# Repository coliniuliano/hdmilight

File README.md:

# HDMI Light v3

Ambilight for a 4K TV, with no PC and no plugin in your media player. One small board sits between your HDMI
source and the TV, watches the picture going past, and drives an LED strip behind the screen so the wall glows
the colours at the edges of the image — in real time, whatever the source is.

## How it works

```mermaid
flowchart LR
    S[HDMI source] --> G[HDMI splitter]
    G -->|4K60, untouched| TV[TV]
    G -->|1080p copy| M[capture chip]
    M -->|USB video| E[ESP32]
    E --> L[LED strip]
```

- An **HDMI splitter** (GSV2001) sends the picture straight on to the TV — 4K60 with HDR, nothing re-encoded or
  delayed — and makes a second, smaller copy. It answers the source's HDCP 2.2, so streaming boxes are happy.
- A **capture chip** (MS2130) turns that copy into a USB video stream, the way a cheap capture stick does.
- An **ESP32-S31** decodes it 30 times a second and drives the strip. `core/` is
  [HyperHDR](https://github.com/awawa-dev/HyperHDR)'s colour pipeline recompiled for a microcontroller — the same
  HDR tone mapping, black-bar detection and smoothing, rewritten in portable C (MIT, `core/LICENSE.HyperHDR`).

All three sit on one 78 × 60 mm board. You set it up from a web page it serves, and it appears in Home Assistant
as a light. The LEDs never depend on your network: unplug the router and they keep following the picture.

## Getting one going

You need the board, a 5 V 1.5 A USB-C supply, two HDMI cables, and a WS2812, WS2815, WS2811 or SK6812 RGBW strip
on its own 5 V supply with the grounds joined and data into J4. (94 LEDs at full white draw about 5.6 A, so
brightness is capped at 60 % by default.)

**Order the board** at [JLCPCB](https://jlcpcb.com): zip up `hardware/fab/gerbers/` and upload it — 4 layers,
1.6 mm, stackup JLC04161H-7628, impedance control, top-side assembly — with `fab/bom_jlcpcb.csv` and
`fab/cpl_jlcpcb.csv`, and check the rotations in their placement preview. Four parts come back unfitted and go on
by hand: the splitter U2 (QFN-76, hot air), the ESP32 module U1, and the headers J4 and J5.

**Flash it** with [ESP-IDF](https://docs.espressif.com/projects/esp-idf/) 6.1 or newer:

```bash
cd firmware && ./idf-oneboard.sh set-target esp32s31 && ./idf-oneboard.sh build
```

```bash
./idf-oneboard.sh -p /dev/cu.usbmodem* flash monitor
```

The capture chip's own flash arrives blank and is written once over the same cable with
`tools/ms2130_serial.py write <image>`. Later updates go over Wi-Fi (`tools/ota_paced.py`), into one of two app
slots, and roll back on their own if the new image cannot reach the network.

**Set it up**: the board puts up its own Wi-Fi network, `hdmilight-xxxx`, password `hdmilight`, with a page at
`http://192.168.4.1`. Pick your network and a name and it answers at `http://<name>.local/` from then on — live
view, strip layout, brightness, colour, HDR, logs, self-test and updates, all also under `/api/`. There is no
password on that page, so keep the board on a network you trust.

The LEDs fade out shortly after the TV goes to standby and come back when it wakes (the page has TV on/off
buttons over CEC), and two seconds after the picture stops.

## What is in here

| Folder | |
|---|---|
| `firmware/` | the ESP-IDF project; `main/www/index.html` is the whole web UI |
| `core/` | the colour pipeline — portable C, no ESP-IDF, tested on the host |
| `hardware/` | the board: a KiCad project generated by the scripts in `gen/`, order files in `fab/` |
| `gsv2001/` | the HDMI splitter driver, its tests, and the tools that check it against the real thing |
| `ms2130/` | tools for the capture chip's flash image |
| `tools/` | updating, flashing, crash decoding and host tests |

Everything is testable without hardware; `make -C core test` and `make -C gsv2001 check` matter most.

---

The board — netlist, hand-scripted routing, fabrication files — and its firmware were made with Claude Fable 5.2,
which also brought the first one up with Colin at the bench.

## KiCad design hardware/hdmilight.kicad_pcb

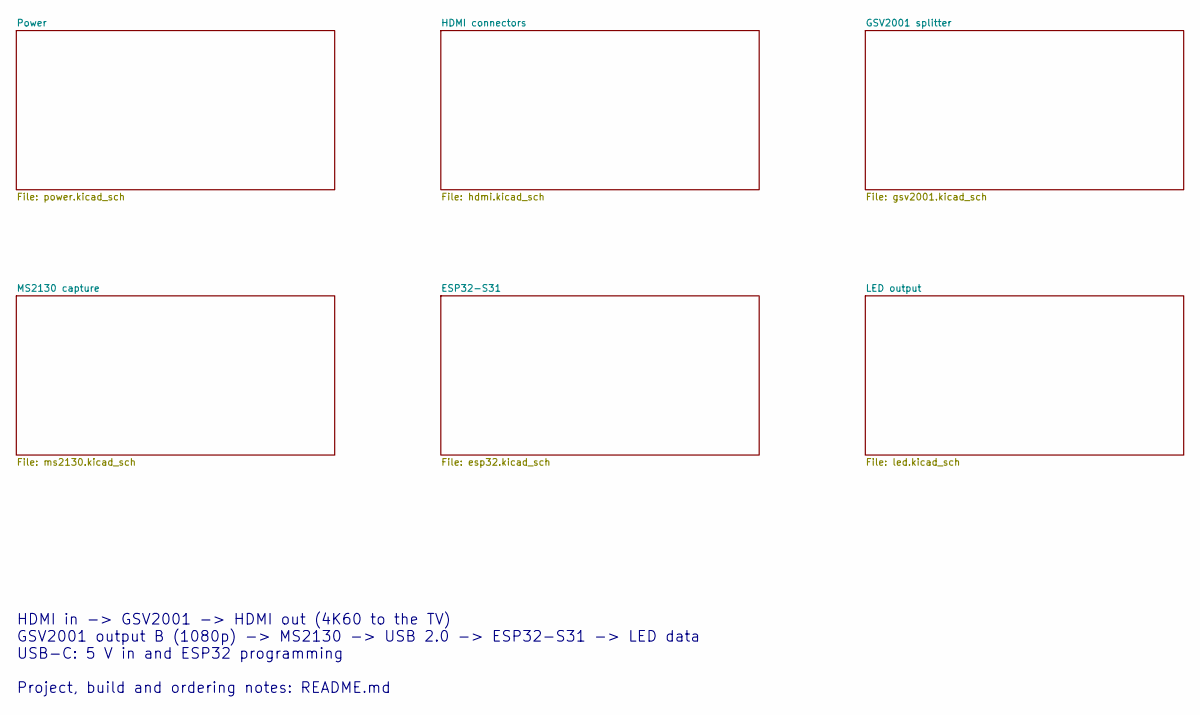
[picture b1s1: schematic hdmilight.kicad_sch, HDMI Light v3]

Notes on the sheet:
HDMI in -> GSV2001 -> HDMI out (4K60 to the TV) GSV2001 output B (1080p) -> MS2130 -> USB 2.0 -> ESP32-S31 -> LED data USB-C: 5 V in and ESP32 programming Project, build and ordering notes: README.md

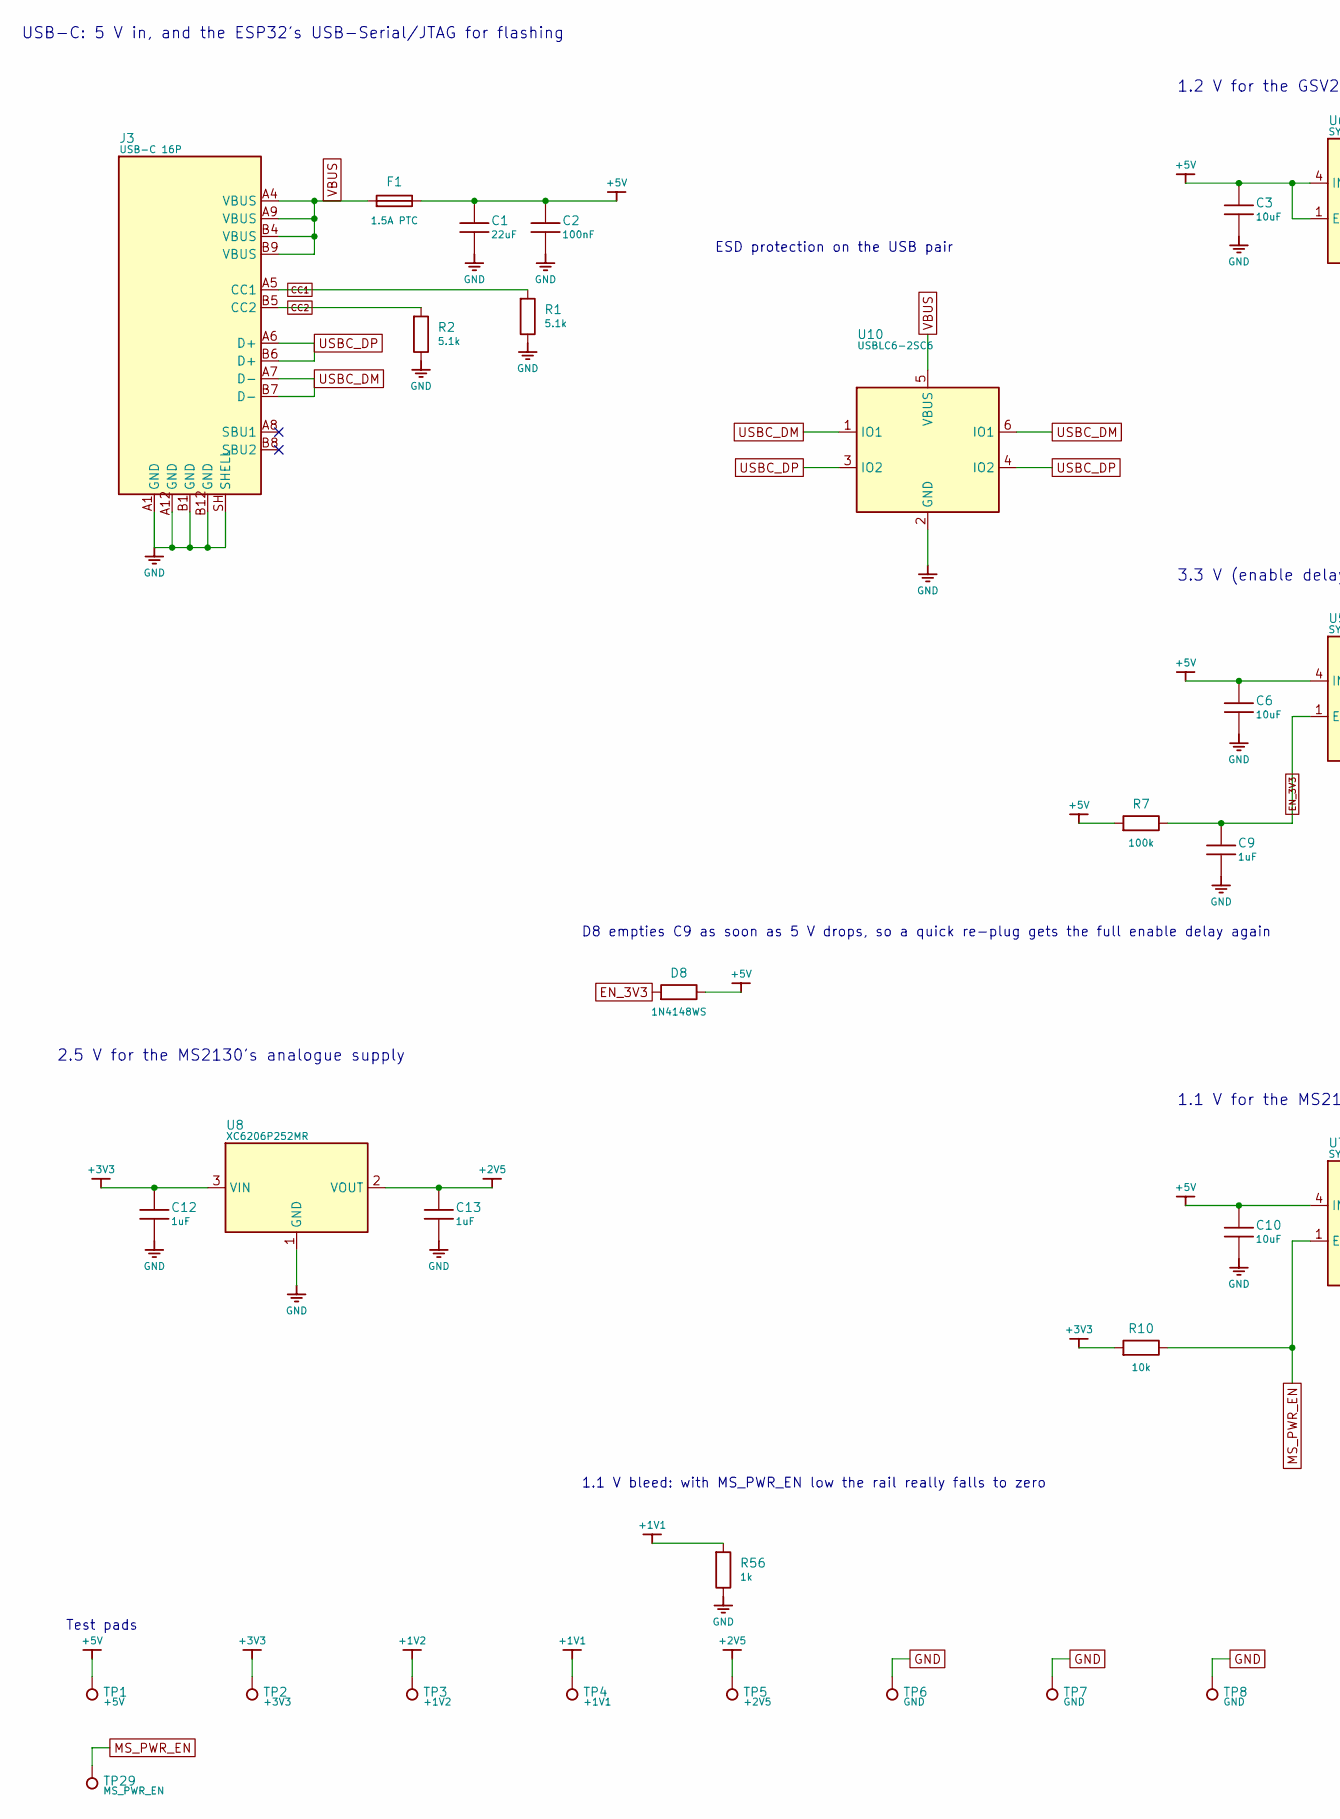
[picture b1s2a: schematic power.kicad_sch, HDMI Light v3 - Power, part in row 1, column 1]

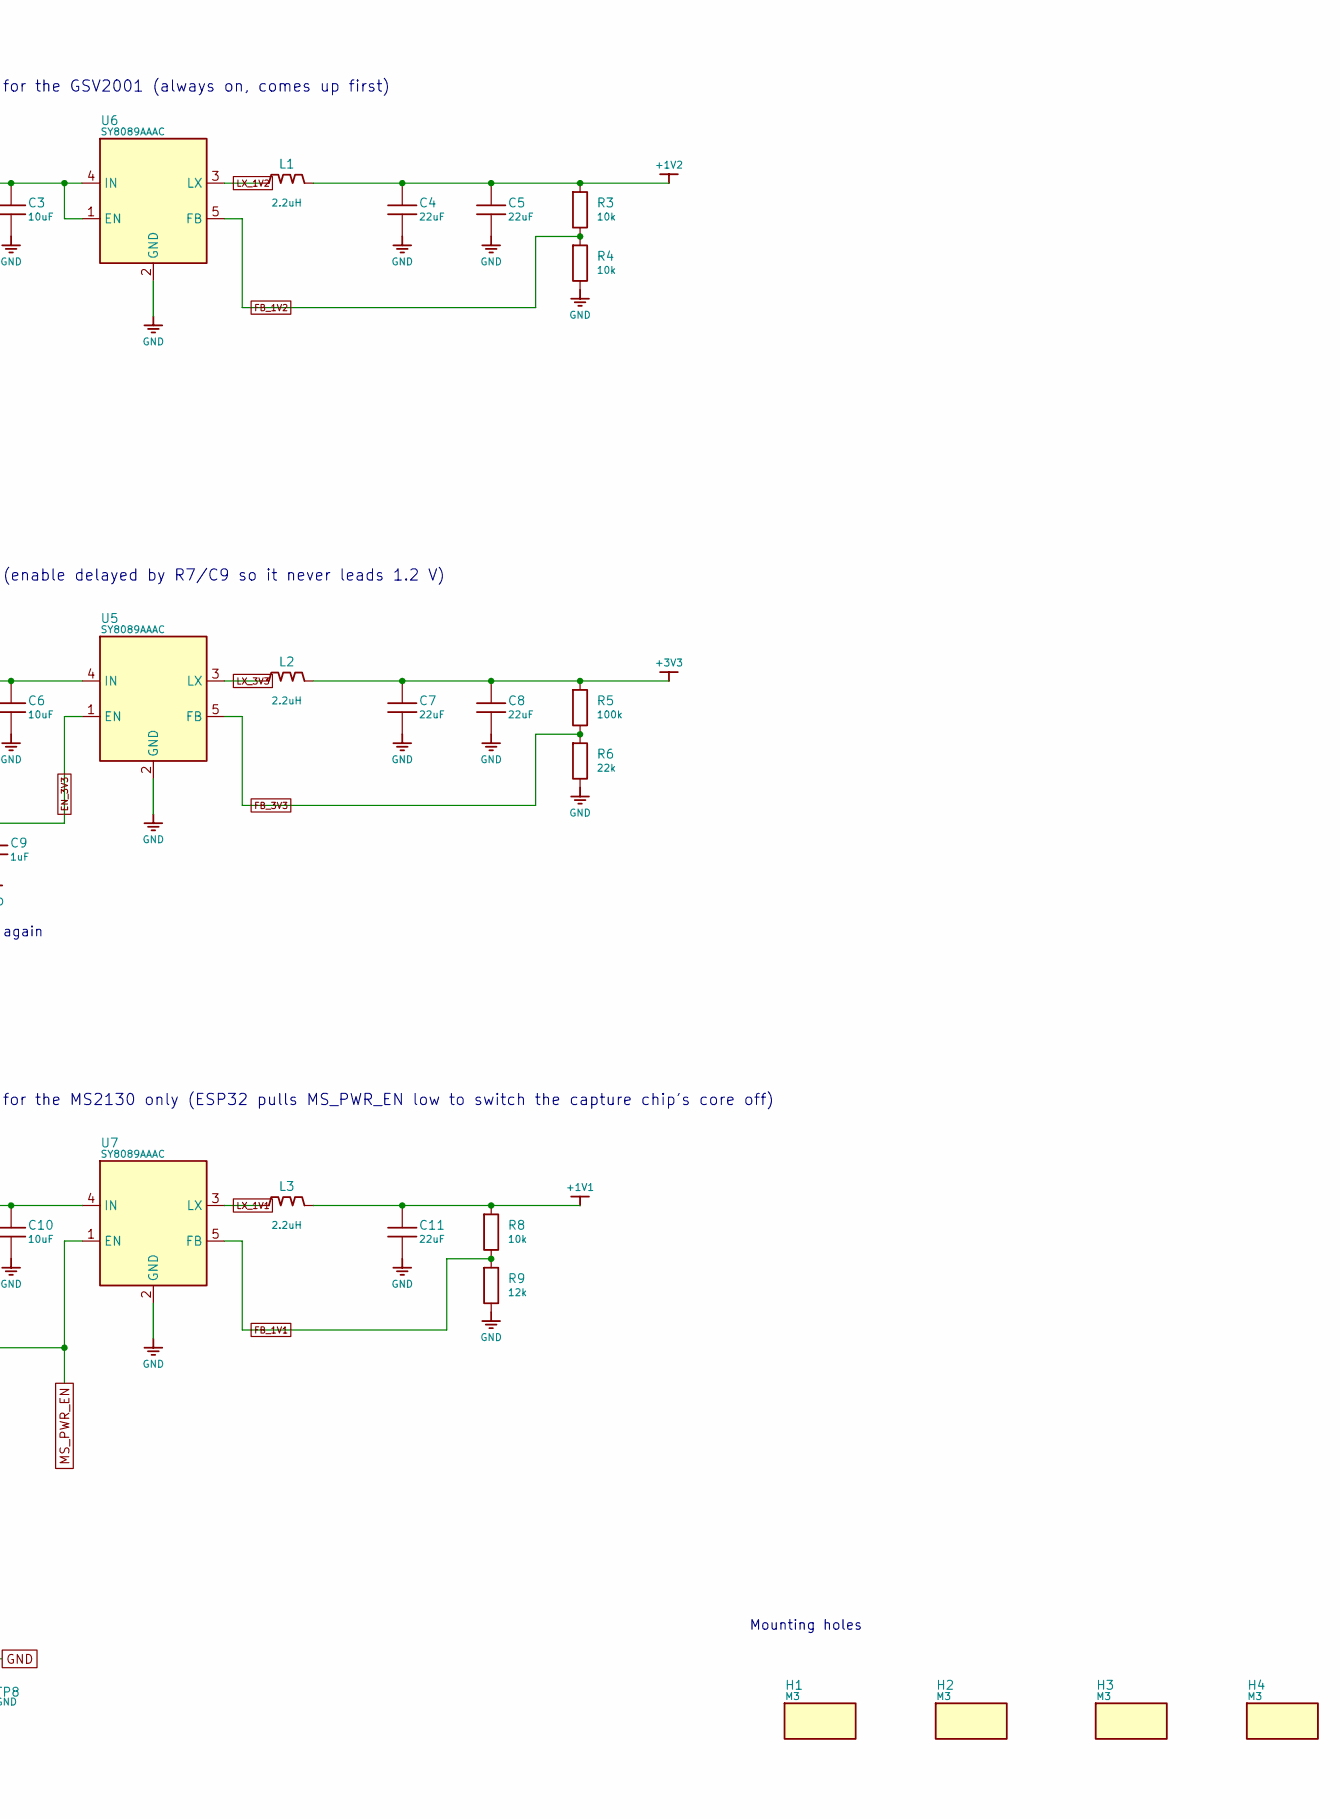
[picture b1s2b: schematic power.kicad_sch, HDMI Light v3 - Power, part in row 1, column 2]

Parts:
C1, C4, C5, C7, C8, C11: 22uF; C_0805_2012Metric; LCSC C45783
C2: 100nF; C_0603_1608Metric; LCSC C14663
C3, C6, C10: 10uF; C_0603_1608Metric; LCSC C19702
C9, C12, C13: 1uF; C_0603_1608Metric; LCSC C15849
D8: 1N4148WS; D_SOD-323; MPN 1N4148WS; LCSC C2128
F1: 1.5A PTC; Fuse_1206_3216Metric; MPN BSMD1206-150-16V; LCSC C883133
H1, H2, H3, H4: M3; MountingHole_3.2mm_M3
J3: USB-C 16P; USB_C_Receptacle_HRO_TYPE-C-31-M-12; MPN TYPE-C-31-M-12; LCSC C165948
L1, L2, L3: 2.2uH; L_Changjiang_FNR3012S; MPN SWPA3015S2R2MT; LCSC C43389
R1, R2: 5.1k; R_0603_1608Metric; LCSC C23186
R3, R4, R8, R10: 10k; R_0603_1608Metric; LCSC C25804
R5, R7: 100k; R_0603_1608Metric; LCSC C25803
R6: 22k; R_0603_1608Metric; LCSC C31850
R9: 12k; R_0603_1608Metric; LCSC C22790
R56: 1k; R_0603_1608Metric; LCSC C21190
TP1: +5V; TestPoint_Pad_D1.0mm
TP2: +3V3; TestPoint_Pad_D1.0mm
TP3: +1V2; TestPoint_Pad_D1.0mm
TP4: +1V1; TestPoint_Pad_D1.0mm
TP5: +2V5; TestPoint_Pad_D1.0mm
TP6, TP7, TP8: GND; TestPoint_Pad_D1.0mm
TP29: MS_PWR_EN; TestPoint_Pad_D1.0mm
U5, U6, U7: SY8089AAAC; SOT-23-5; MPN SY8089AAAC; LCSC C78988
U8: XC6206P252MR; SOT-23; MPN XC6206P252MR; LCSC C545580
U10: USBLC6-2SC6; SOT-23-6; MPN USBLC6-2SC6; LCSC C7519

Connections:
+1V1: C11.1, L3.2, R8.1, R56.1, TP4.1; also elsewhere on the board
+1V2: C4.1, C5.1, L1.2, R3.1, TP3.1; also elsewhere on the board
+2V5: C13.1, TP5.1, U8.2 (VOUT); also elsewhere on the board
+3V3: C7.1, C8.1, C12.1, L2.2, R5.1, R10.1, TP2.1, U8.3 (VIN); also elsewhere on the board
+5V: C1.1, C2.1, C3.1, C6.1, C10.1, D8.1, F1.2, R7.1, TP1.1, U5.4 (IN), U6.1 (EN), U6.4 (IN), U7.4 (IN); also elsewhere on the board
CC1: J3.A5 (CC1), R1.1
CC2: J3.B5 (CC2), R2.1
EN_3V3: C9.1, D8.2, R7.2, U5.1 (EN)
FB_1V1: R8.2, R9.1, U7.5 (FB)
FB_1V2: R3.2, R4.1, U6.5 (FB)
FB_3V3: R5.2, R6.1, U5.5 (FB)
GND: C1.2, C2.2, C3.2, C4.2, C5.2, C6.2, C7.2, C8.2, C9.2, C10.2, C11.2, C12.2, C13.2, J3.A1 (GND), J3.A12 (GND), J3.B1 (GND), J3.B12 (GND), J3.SH (SHELL), R1.2, R2.2, R4.2, R6.2, R9.2, R56.2, TP6.1, TP7.1, TP8.1, U5.2 (GND), U6.2 (GND), U7.2 (GND), U8.1 (GND), U10.2 (GND); also elsewhere on the board
LX_1V1: L3.1, U7.3 (LX)
LX_1V2: L1.1, U6.3 (LX)
LX_3V3: L2.1, U5.3 (LX)
MS_PWR_EN: R10.2, TP29.1, U7.1 (EN); also elsewhere on the board
USBC_DM: J3.A7 (D-), J3.B7 (D-), U10.1 (IO1), U10.6 (IO1); also elsewhere on the board
USBC_DP: J3.A6 (D+), J3.B6 (D+), U10.3 (IO2), U10.4 (IO2); also elsewhere on the board
VBUS: F1.1, J3.A4 (VBUS), J3.A9 (VBUS), J3.B4 (VBUS), J3.B9 (VBUS), U10.5 (VBUS)

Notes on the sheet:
USB-C: 5 V in, and the ESP32's USB-Serial/JTAG for flashing
ESD protection on the USB pair
1.2 V for the GSV2001 (always on, comes up first)
3.3 V (enable delayed by R7/C9 so it never leads 1.2 V)
1.1 V for the MS2130 only (ESP32 pulls MS_PWR_EN low to switch the capture chip's core off)
2.5 V for the MS2130's analogue supply
Test pads
D8 empties C9 as soon as 5 V drops, so a quick re-plug gets the full enable delay again
1.1 V bleed: with MS_PWR_EN low the rail really falls to zero
Mounting holes

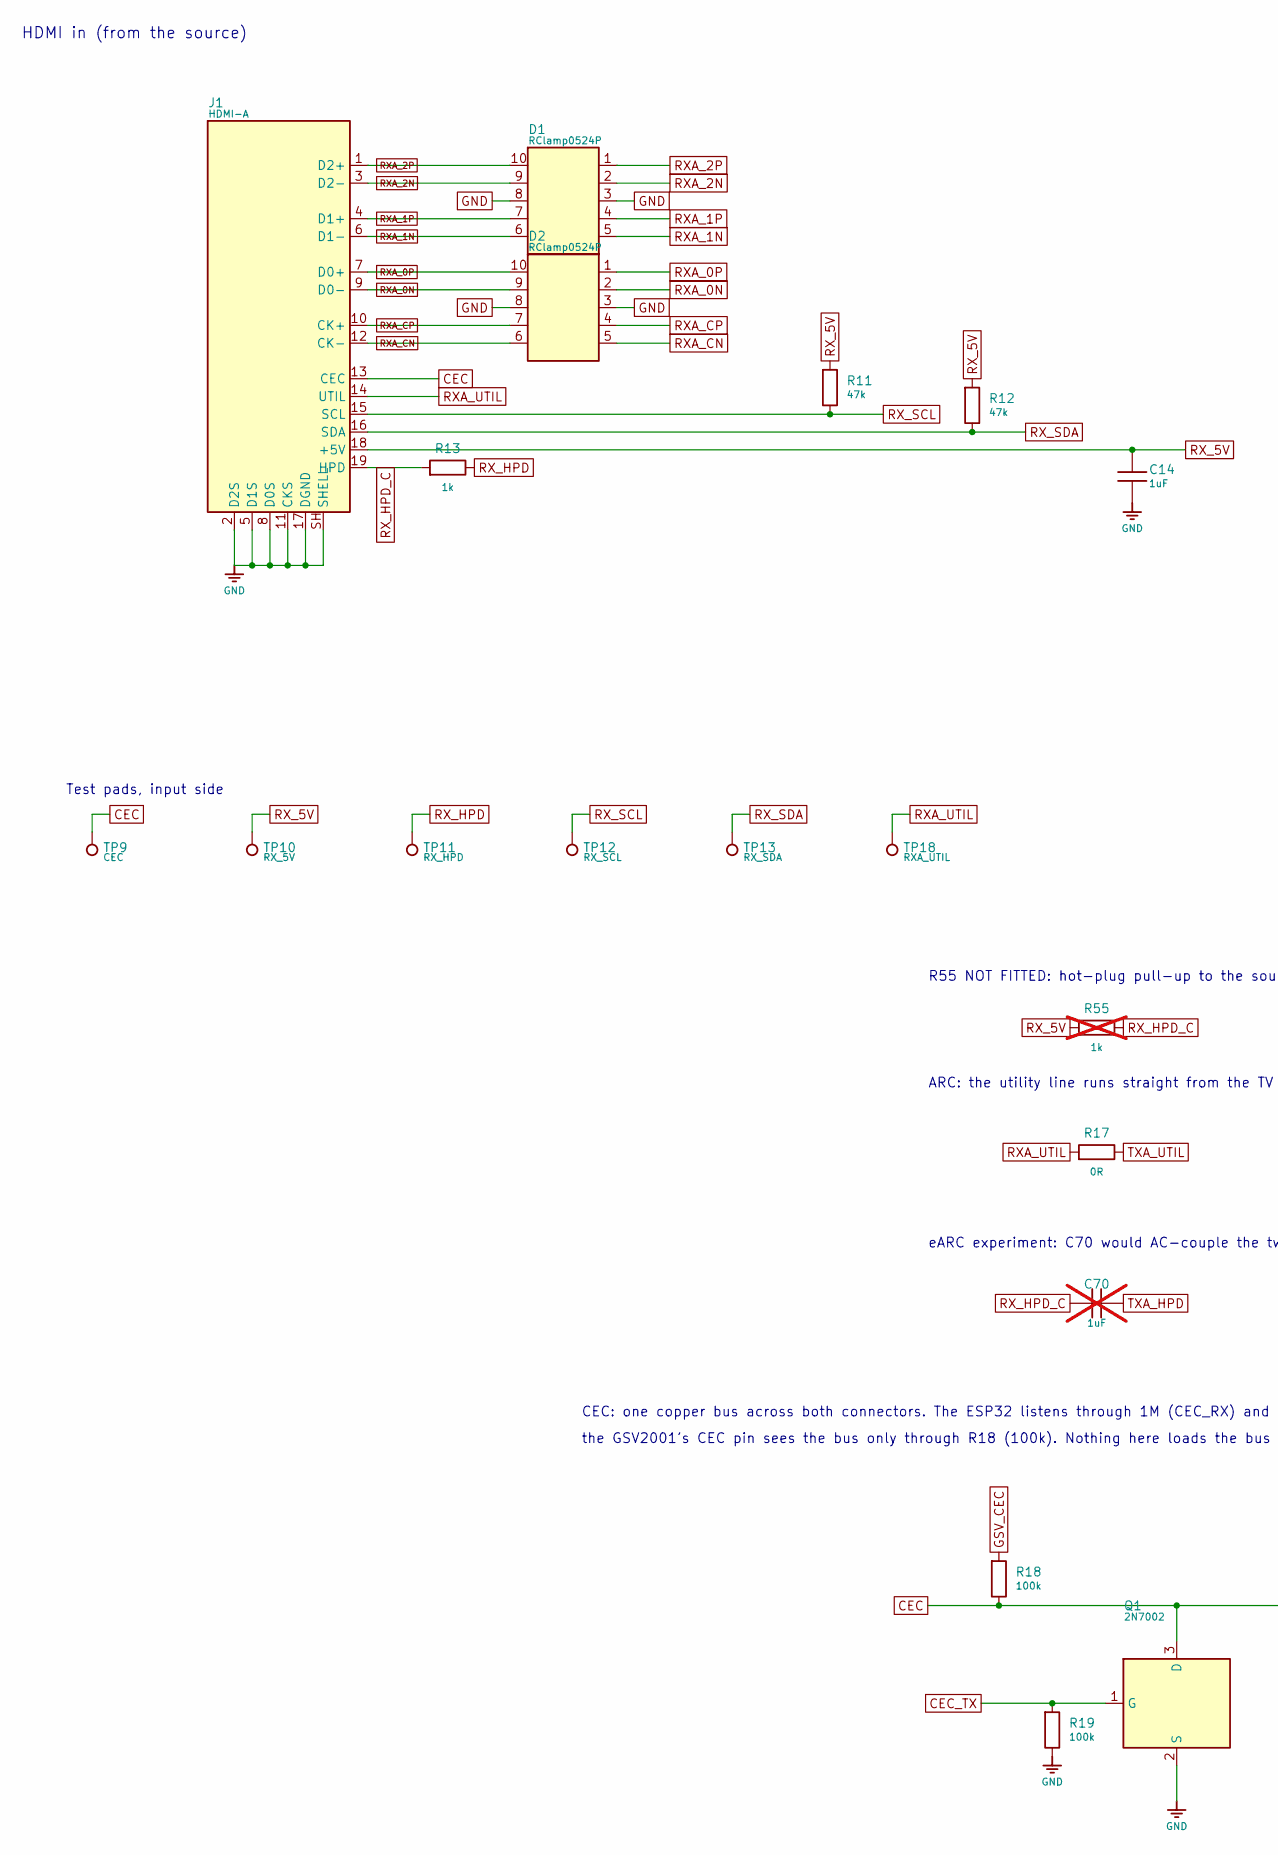
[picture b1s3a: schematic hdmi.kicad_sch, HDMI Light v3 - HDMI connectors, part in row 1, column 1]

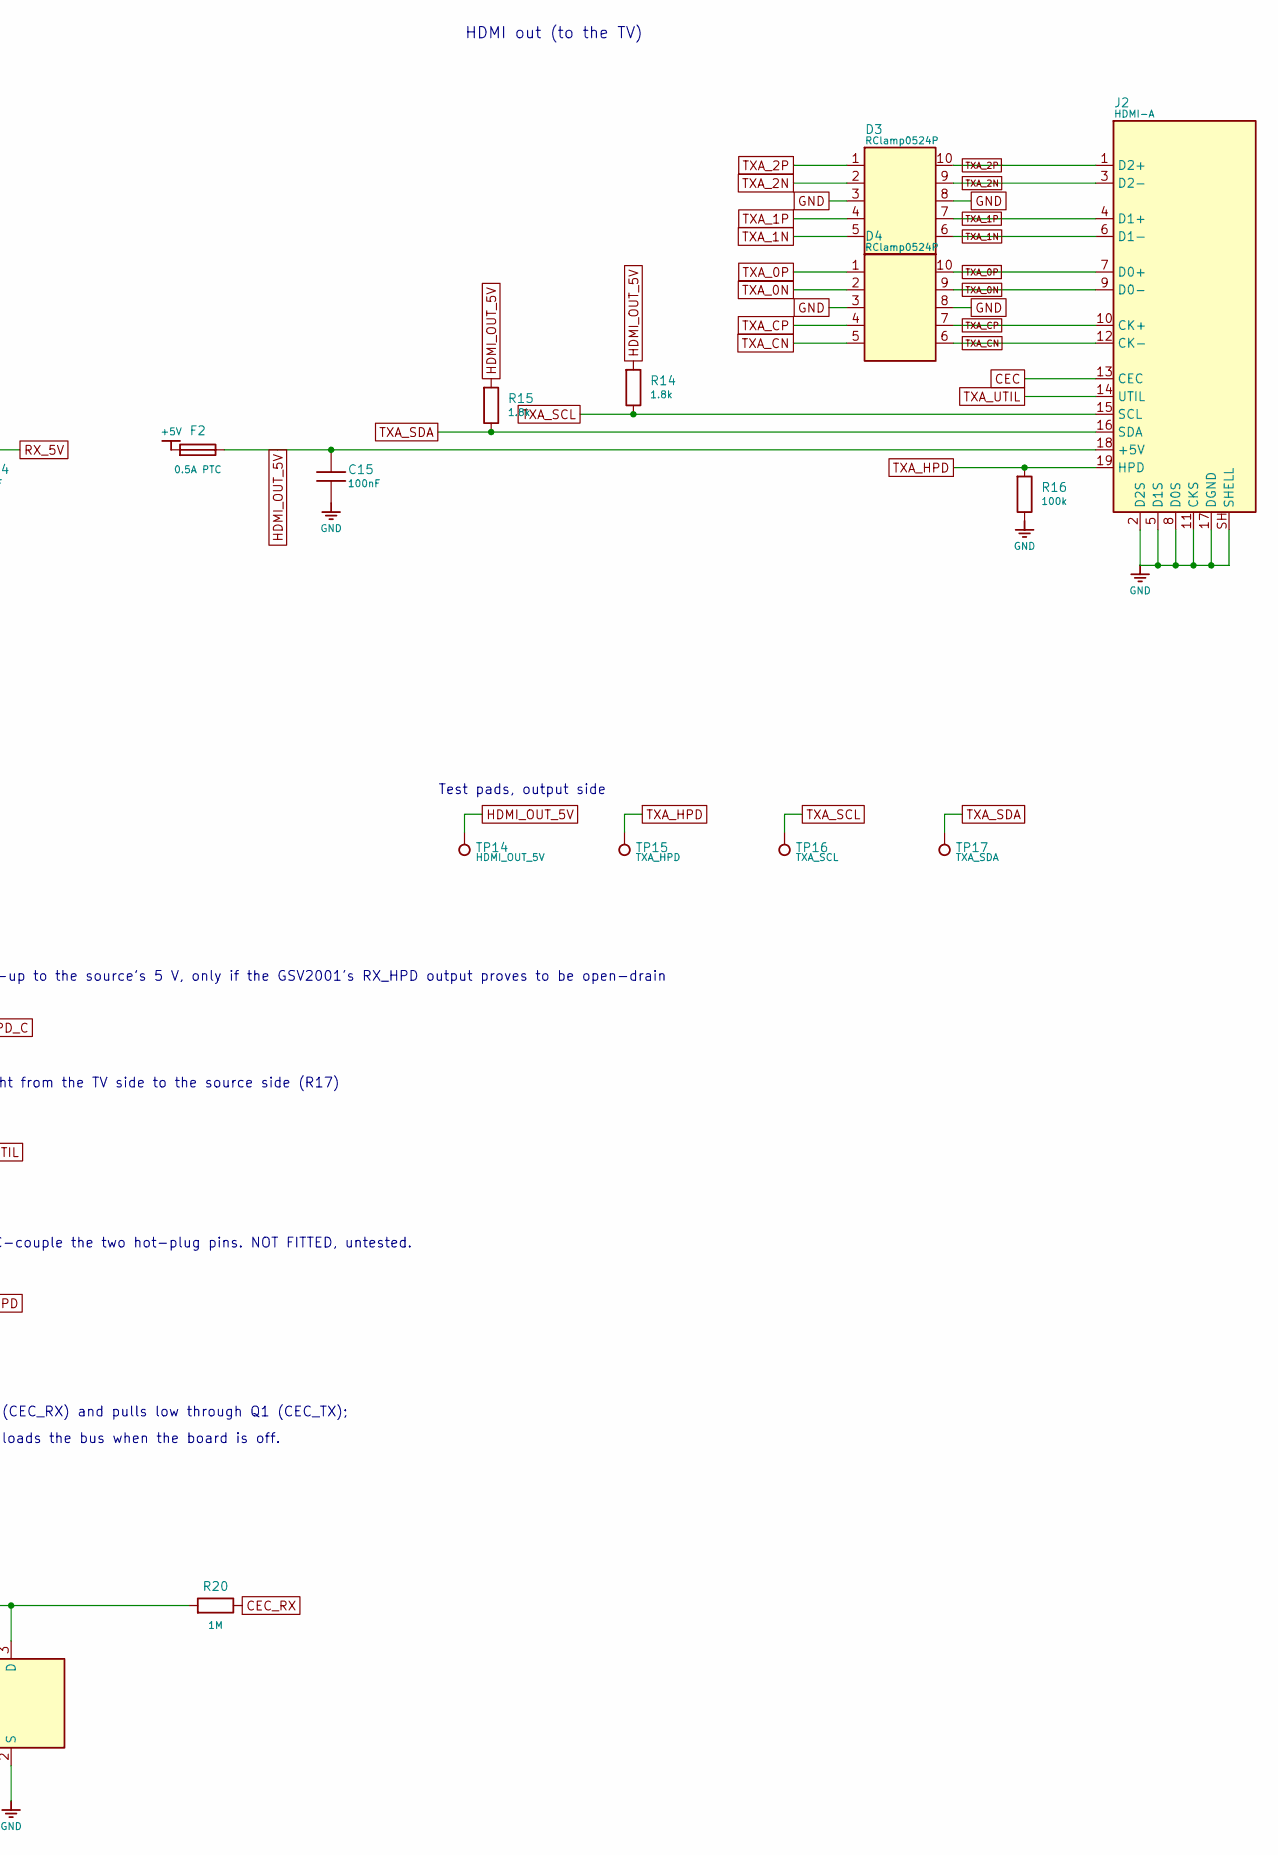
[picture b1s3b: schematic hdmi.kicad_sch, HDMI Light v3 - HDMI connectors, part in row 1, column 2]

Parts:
C14: 1uF; C_0603_1608Metric; LCSC C15849
C15: 100nF; C_0603_1608Metric; LCSC C14663
C70: 1uF; C_0603_1608Metric; LCSC C15849; not fitted
D1, D2, D3, D4: RClamp0524P; USON-10_2.5x1.0mm_P0.5mm; MPN RClamp0524PATCT; LCSC C40960
F2: 0.5A PTC; Fuse_1206_3216Metric; MPN JK-nSMD050-30; LCSC C720075
J1, J2: HDMI-A; HDMI_A_Amphenol_10029449-x01xLF_Horizontal; MPN 10029449-111RLF; LCSC C427307
Q1: 2N7002; SOT-23; MPN 2N7002; LCSC C8545
R11, R12: 47k; R_0603_1608Metric; LCSC C25819
R13: 1k; R_0603_1608Metric; LCSC C21190
R14, R15: 1.8k; R_0603_1608Metric; LCSC C4177
R16, R18, R19: 100k; R_0603_1608Metric; LCSC C25803
R17: 0R; R_0603_1608Metric; LCSC C21189
R20: 1M; R_0603_1608Metric; LCSC C22935
R55: 1k; R_0603_1608Metric; LCSC C21190; not fitted
TP9: CEC; TestPoint_Pad_D1.0mm
TP10: RX_5V; TestPoint_Pad_D1.0mm
TP11: RX_HPD; TestPoint_Pad_D1.0mm
TP12: RX_SCL; TestPoint_Pad_D1.0mm
TP13: RX_SDA; TestPoint_Pad_D1.0mm
TP14: HDMI_OUT_5V; TestPoint_Pad_D1.0mm
TP15: TXA_HPD; TestPoint_Pad_D1.0mm
TP16: TXA_SCL; TestPoint_Pad_D1.0mm
TP17: TXA_SDA; TestPoint_Pad_D1.0mm
TP18: RXA_UTIL; TestPoint_Pad_D1.0mm

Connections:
+5V: F2.1; also elsewhere on the board
CEC: J1.13 (CEC), J2.13 (CEC), Q1.3 (D), R18.2, R20.1, TP9.1
CEC_RX: R20.2; also elsewhere on the board
CEC_TX: Q1.1 (G), R19.1; also elsewhere on the board
GND: C14.2, C15.2, D1.3, D1.8, D2.3, D2.8, D3.3, D3.8, D4.3, D4.8, J1.2 (D2S), J1.5 (D1S), J1.8 (D0S), J1.11 (CKS), J1.17 (DGND), J1.SH (SHELL), J2.2 (D2S), J2.5 (D1S), J2.8 (D0S), J2.11 (CKS), J2.17 (DGND), J2.SH (SHELL), Q1.2 (S), R16.2, R19.2; also elsewhere on the board
GSV_CEC: R18.1; also elsewhere on the board
HDMI_OUT_5V: C15.1, F2.2, J2.18 (+5V), R14.1, R15.1, TP14.1
RXA_0N: D2.2, D2.9, J1.9 (D0-); also elsewhere on the board
RXA_0P: D2.1, D2.10, J1.7 (D0+); also elsewhere on the board
RXA_1N: D1.5, D1.6, J1.6 (D1-); also elsewhere on the board
RXA_1P: D1.4, D1.7, J1.4 (D1+); also elsewhere on the board
RXA_2N: D1.2, D1.9, J1.3 (D2-); also elsewhere on the board
RXA_2P: D1.1, D1.10, J1.1 (D2+); also elsewhere on the board
RXA_CN: D2.5, D2.6, J1.12 (CK-); also elsewhere on the board
RXA_CP: D2.4, D2.7, J1.10 (CK+); also elsewhere on the board
RXA_UTIL: J1.14 (UTIL), R17.1, TP18.1
RX_5V: C14.1, J1.18 (+5V), R11.1, R12.1, R55.1, TP10.1; also elsewhere on the board
RX_HPD: R13.1, TP11.1; also elsewhere on the board
RX_HPD_C: C70.1, J1.19 (HPD), R13.2, R55.2
RX_SCL: J1.15 (SCL), R11.2, TP12.1; also elsewhere on the board
RX_SDA: J1.16 (SDA), R12.2, TP13.1; also elsewhere on the board
TXA_0N: D4.2, D4.9, J2.9 (D0-); also elsewhere on the board
TXA_0P: D4.1, D4.10, J2.7 (D0+); also elsewhere on the board
TXA_1N: D3.5, D3.6, J2.6 (D1-); also elsewhere on the board
TXA_1P: D3.4, D3.7, J2.4 (D1+); also elsewhere on the board
TXA_2N: D3.2, D3.9, J2.3 (D2-); also elsewhere on the board
TXA_2P: D3.1, D3.10, J2.1 (D2+); also elsewhere on the board
TXA_CN: D4.5, D4.6, J2.12 (CK-); also elsewhere on the board
TXA_CP: D4.4, D4.7, J2.10 (CK+); also elsewhere on the board
TXA_HPD: C70.2, J2.19 (HPD), R16.1, TP15.1; also elsewhere on the board
TXA_SCL: J2.15 (SCL), R14.2, TP16.1; also elsewhere on the board
TXA_SDA: J2.16 (SDA), R15.2, TP17.1; also elsewhere on the board
TXA_UTIL: J2.14 (UTIL), R17.2

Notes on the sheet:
HDMI in (from the source)
HDMI out (to the TV)
ARC: the utility line runs straight from the TV side to the source side (R17)
R55 NOT FITTED: hot-plug pull-up to the source's 5 V, only if the GSV2001's RX_HPD output proves to be open-drain
eARC experiment: C70 would AC-couple the two hot-plug pins. NOT FITTED, untested.
CEC: one copper bus across both connectors. The ESP32 listens through 1M (CEC_RX) and pulls low through Q1 (CEC_TX);
the GSV2001's CEC pin sees the bus only through R18 (100k). Nothing here loads the bus when the board is off.
Test pads, input side
Test pads, output side
